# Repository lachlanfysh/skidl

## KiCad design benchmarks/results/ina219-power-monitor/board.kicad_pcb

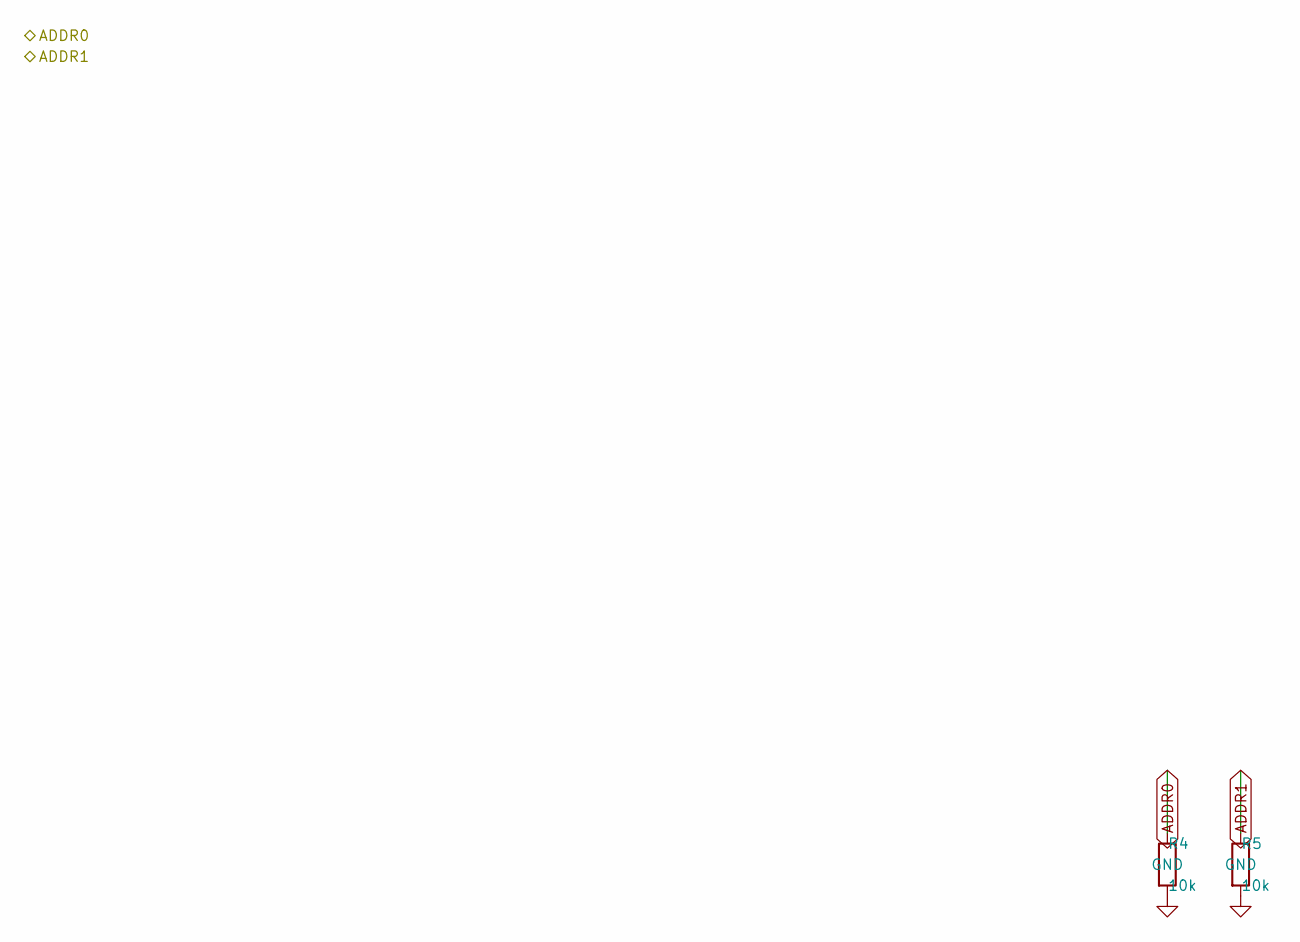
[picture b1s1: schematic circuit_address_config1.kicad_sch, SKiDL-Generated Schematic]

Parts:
R4, R5: 10k; R_0603_1608Metric

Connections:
ADDR0: R4.1; also elsewhere on the board
ADDR1: R5.1; also elsewhere on the board
GND: R4.2, R5.2; also elsewhere on the board

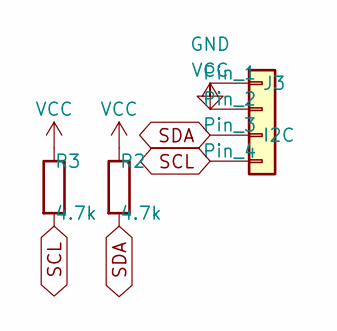
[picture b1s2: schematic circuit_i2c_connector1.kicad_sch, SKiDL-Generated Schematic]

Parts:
J3: I2C; PinHeader_1x04_P2.54mm_Vertical
R2, R3: 4.7k; R_0603_1608Metric

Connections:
GND: J3.1; also elsewhere on the board
SCL: J3.4, R3.2; also elsewhere on the board
SDA: J3.3, R2.2; also elsewhere on the board
VCC: J3.2, R2.1, R3.1; also elsewhere on the board

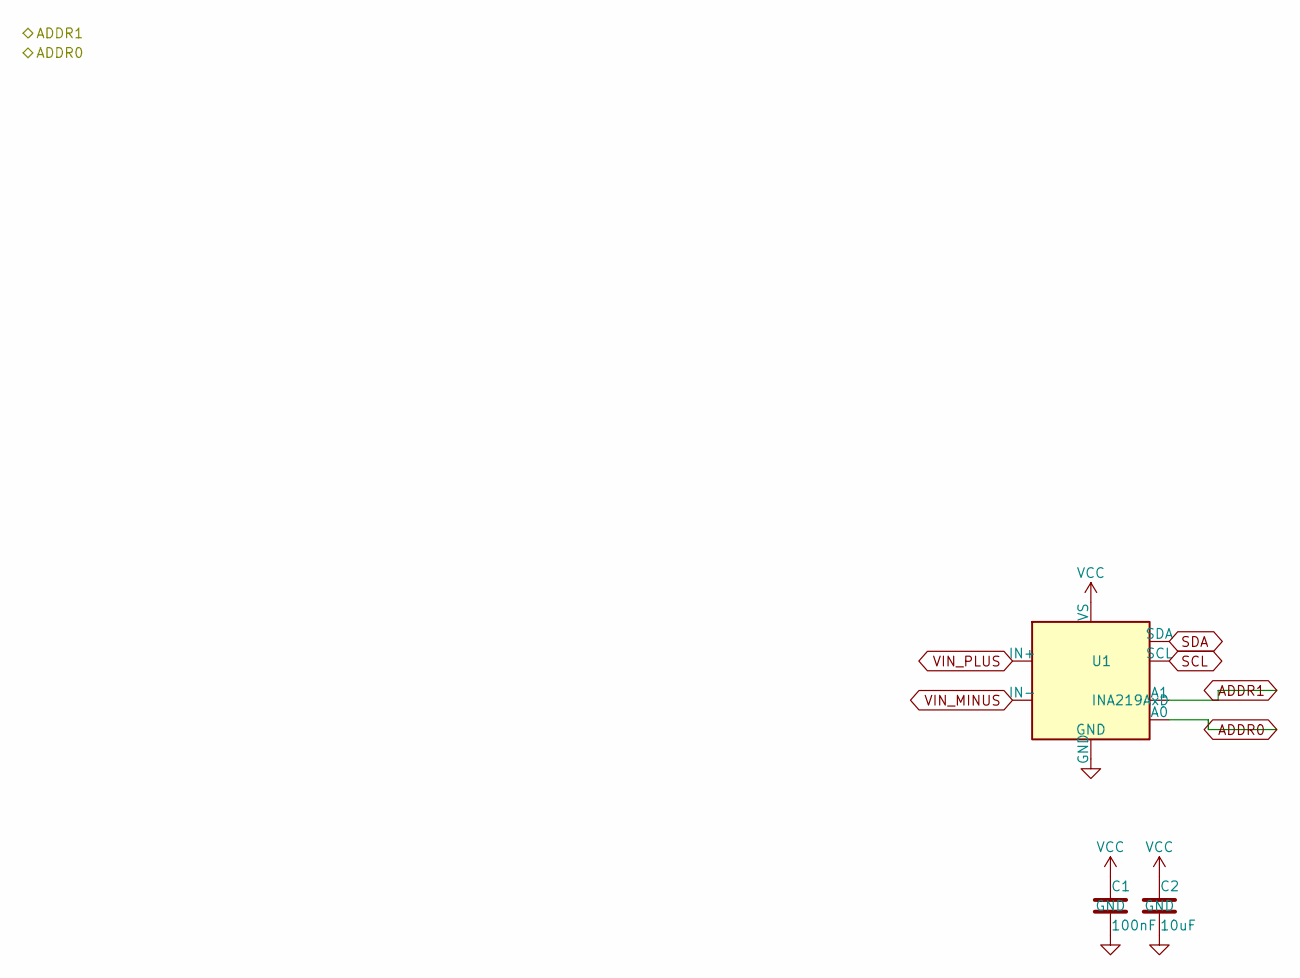
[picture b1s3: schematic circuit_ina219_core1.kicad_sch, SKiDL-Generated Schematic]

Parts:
C1: 100nF; C_0603_1608Metric
C2: 10uF; C_0805_2012Metric
U1: INA219AxD; SOIC-8_3.9x4.9mm_P1.27mm

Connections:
ADDR0: U1.2 (A0); also elsewhere on the board
ADDR1: U1.1 (A1); also elsewhere on the board
GND: C1.2, C2.2, U1.6 (GND); also elsewhere on the board
SCL: U1.4 (SCL); also elsewhere on the board
SDA: U1.3 (SDA); also elsewhere on the board
VCC: C1.1, C2.1, U1.5 (VS); also elsewhere on the board
VIN_MINUS: U1.7 (IN-); also elsewhere on the board
VIN_PLUS: U1.8 (IN+); also elsewhere on the board

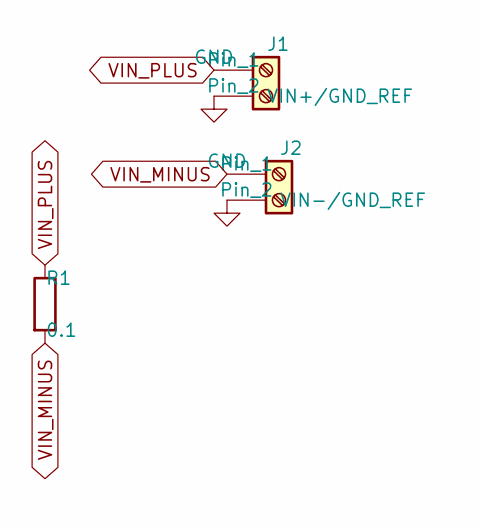
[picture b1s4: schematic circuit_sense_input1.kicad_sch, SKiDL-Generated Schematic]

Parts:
J1: VIN+/GND_REF; TerminalBlock_Phoenix_MKDS-1,5-2-5.08_1x02_P5.08mm_Horizont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
J2: VIN-/GND_REF; TerminalBlock_Phoenix_MKDS-1,5-2-5.08_1x02_P5.08mm_Horizont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
R1: 0.1; R_2512_6332Metric

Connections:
GND: J1.2, J2.2; also elsewhere on the board
VIN_MINUS: J2.1, R1.2; also elsewhere on the board
VIN_PLUS: J1.1, R1.1; also elsewhere on the board

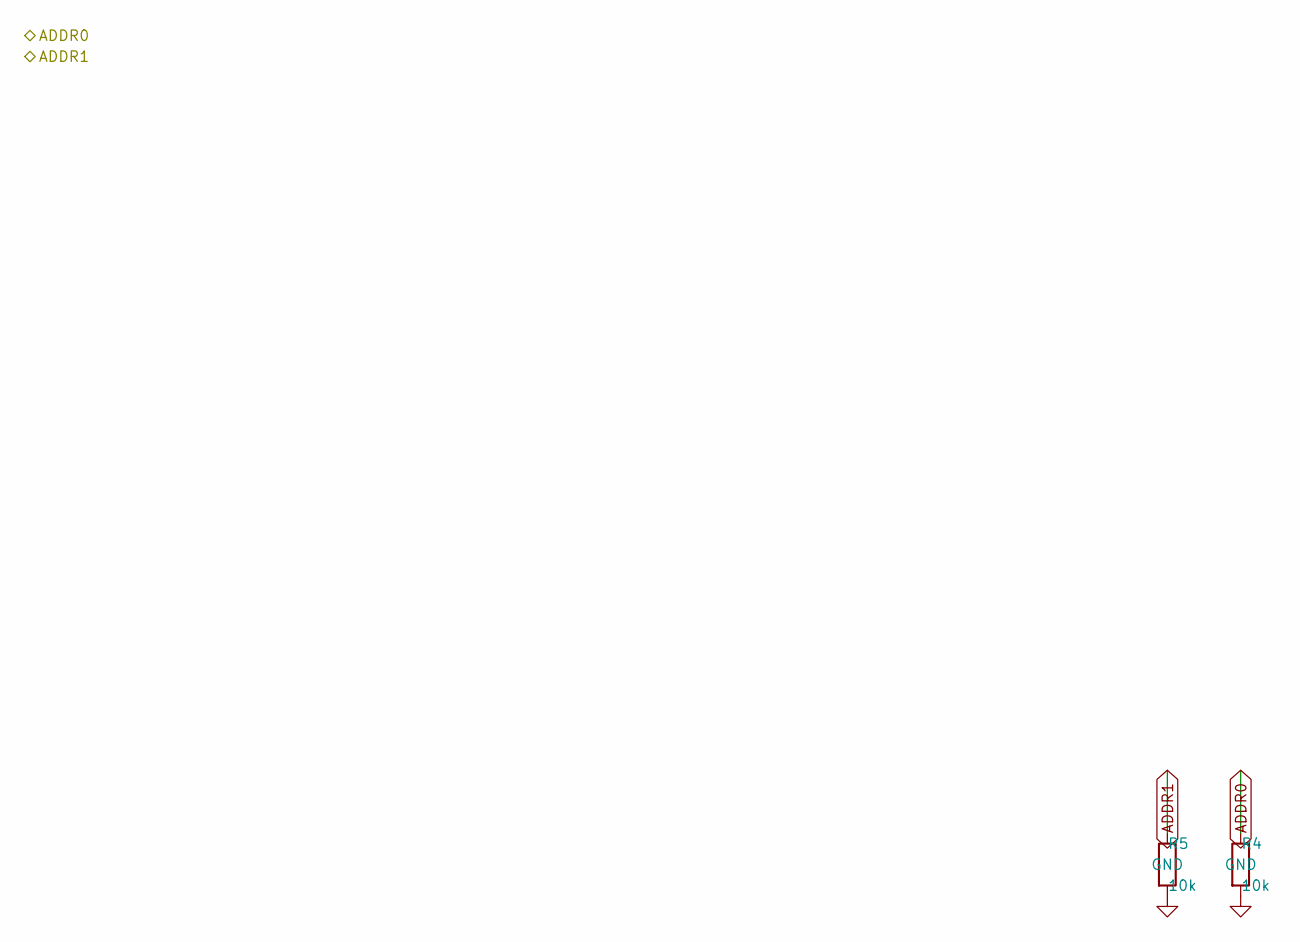
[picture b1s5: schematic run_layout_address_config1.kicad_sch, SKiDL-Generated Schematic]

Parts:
R4, R5: 10k; R_0603_1608Metric

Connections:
ADDR0: R4.1; also elsewhere on the board
ADDR1: R5.1; also elsewhere on the board
GND: R4.2, R5.2; also elsewhere on the board

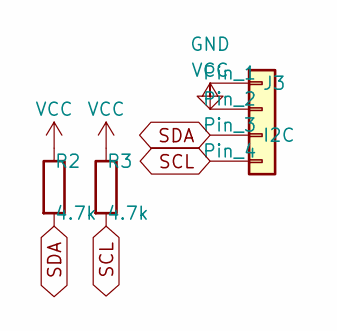
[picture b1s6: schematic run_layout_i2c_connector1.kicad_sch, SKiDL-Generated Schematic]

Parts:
J3: I2C; PinHeader_1x04_P2.54mm_Vertical
R2, R3: 4.7k; R_0603_1608Metric

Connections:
GND: J3.1; also elsewhere on the board
SCL: J3.4, R3.2; also elsewhere on the board
SDA: J3.3, R2.2; also elsewhere on the board
VCC: J3.2, R2.1, R3.1; also elsewhere on the board

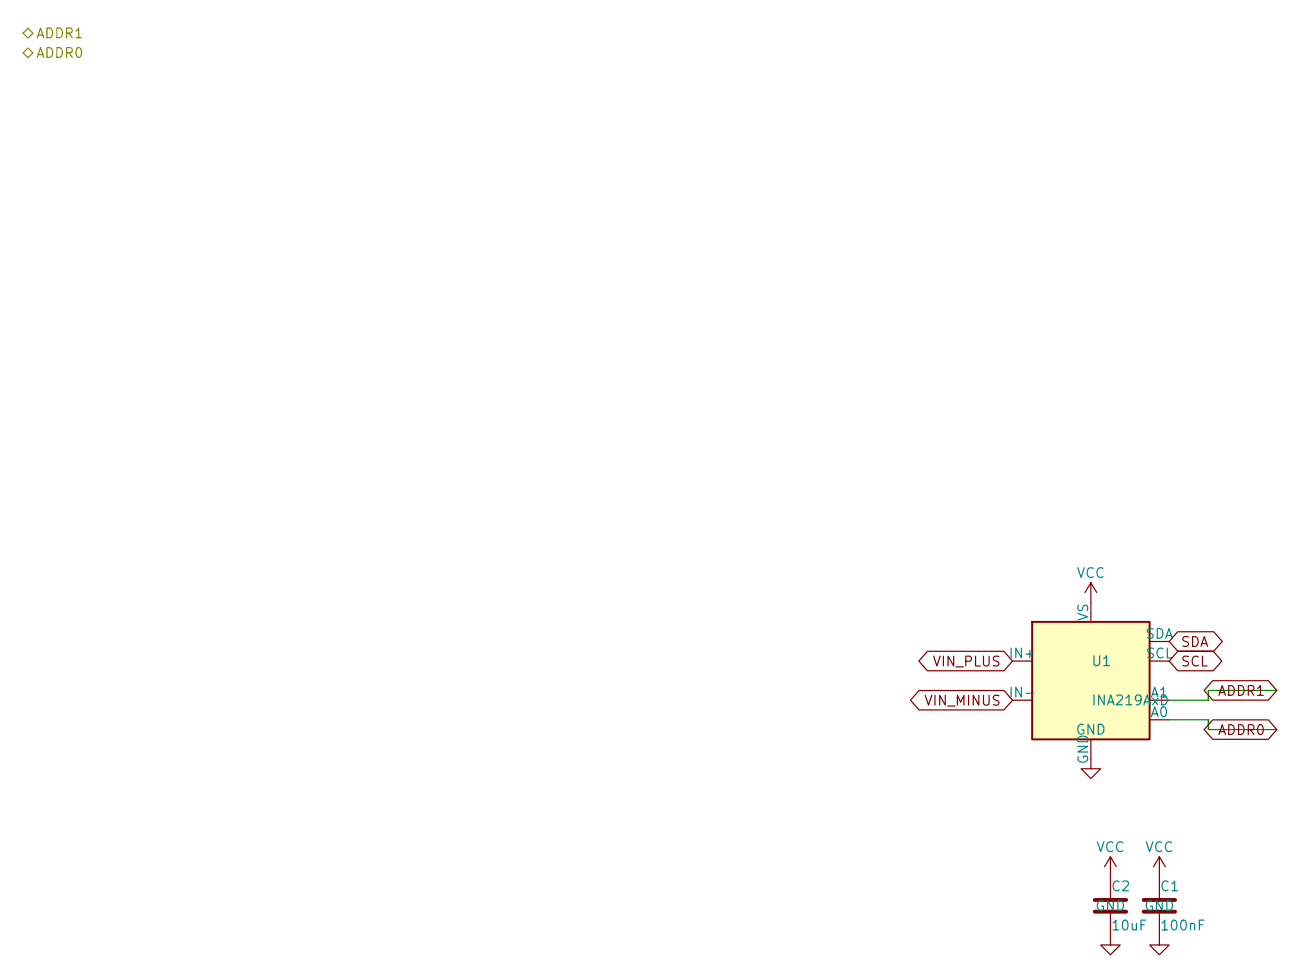
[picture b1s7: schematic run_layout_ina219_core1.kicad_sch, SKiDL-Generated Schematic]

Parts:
C1: 100nF; C_0603_1608Metric
C2: 10uF; C_0805_2012Metric
U1: INA219AxD; SOIC-8_3.9x4.9mm_P1.27mm

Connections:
ADDR0: U1.2 (A0); also elsewhere on the board
ADDR1: U1.1 (A1); also elsewhere on the board
GND: C1.2, C2.2, U1.6 (GND); also elsewhere on the board
SCL: U1.4 (SCL); also elsewhere on the board
SDA: U1.3 (SDA); also elsewhere on the board
VCC: C1.1, C2.1, U1.5 (VS); also elsewhere on the board
VIN_MINUS: U1.7 (IN-); also elsewhere on the board
VIN_PLUS: U1.8 (IN+); also elsewhere on the board

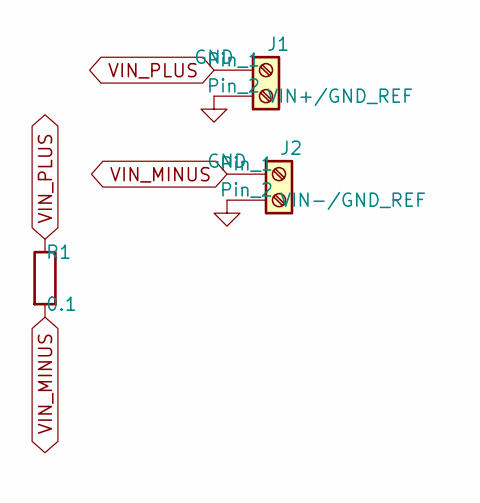
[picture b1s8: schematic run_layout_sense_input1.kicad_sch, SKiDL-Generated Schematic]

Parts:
J1: VIN+/GND_REF; TerminalBlock_Phoenix_MKDS-1,5-2-5.08_1x02_P5.08mm_Horizont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
J2: VIN-/GND_REF; TerminalBlock_Phoenix_MKDS-1,5-2-5.08_1x02_P5.08mm_Horizont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
R1: 0.1; R_2512_6332Metric

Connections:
GND: J1.2, J2.2; also elsewhere on the board
VIN_MINUS: J2.1, R1.2; also elsewhere on the board
VIN_PLUS: J1.1, R1.1; also elsewhere on the board

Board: 2 copper layers, 11 parts (0 on the bottom side), 8 nets, no tracks yet.

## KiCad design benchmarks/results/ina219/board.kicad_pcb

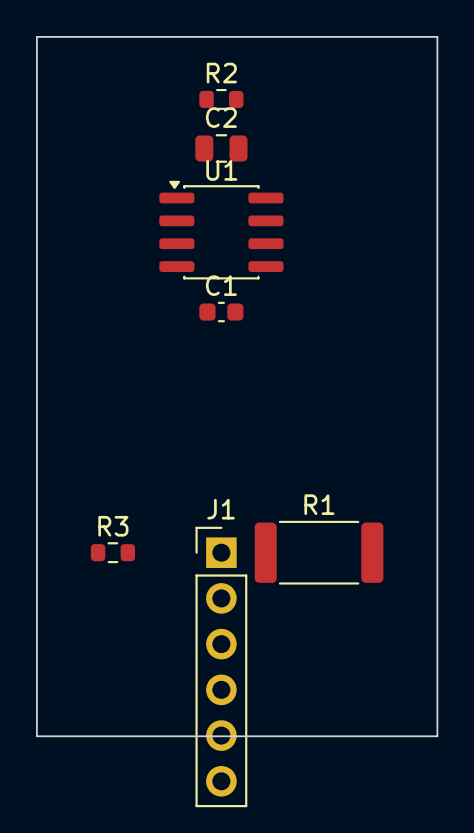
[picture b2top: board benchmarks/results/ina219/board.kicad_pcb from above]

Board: 2 copper layers, 22.2 x 38.9 mm, 7 parts (0 on the bottom side), 6 nets, no tracks yet.

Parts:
C1: 100nF; C_0603_1608Metric
C2: 10uF; C_0805_2012Metric
J1: Breakout_Header; PinHeader_1x06_P2.54mm_Vertical
R1: 0.1; R_2512_6332Metric
R2, R3: 10K; R_0603_1608Metric
U1: INA219BxD; SOIC-8_3.9x4.9mm_P1.27mm

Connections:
GND: C1.2, C2.2, J1.2, U1.1, U1.2, U1.6
SCL: J1.3, R3.2, U1.4
SDA: J1.4, R2.2, U1.3
VCC: C1.1, C2.1, J1.1, R2.1, R3.1, U1.5
VIN+: J1.5, R1.1, U1.8
VIN-: J1.6, R1.2, U1.7

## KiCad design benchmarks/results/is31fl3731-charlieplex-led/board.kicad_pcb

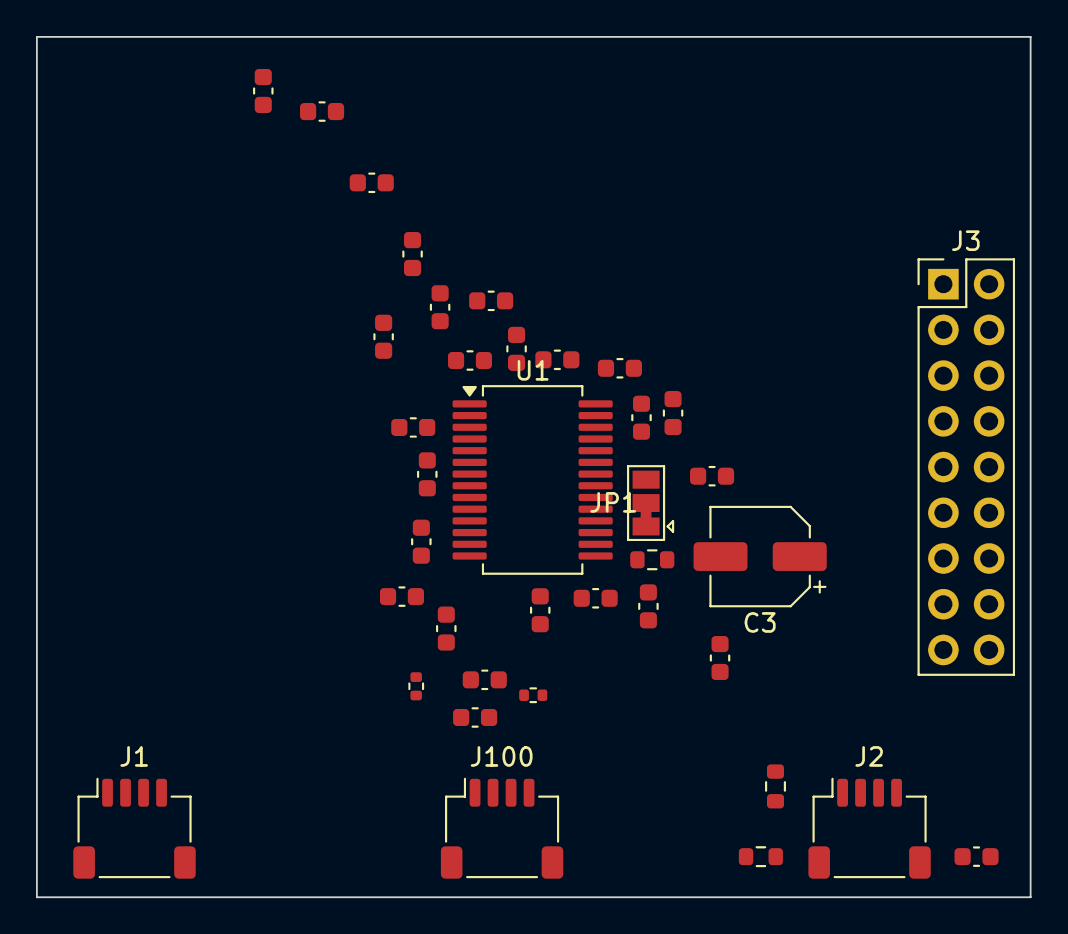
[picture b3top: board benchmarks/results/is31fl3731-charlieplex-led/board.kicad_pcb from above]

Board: 2 copper layers, 55.2 x 47.8 mm, 38 parts (0 on the bottom side), 27 nets, no tracks yet.

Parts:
C1: 220nF; C_0603_1608Metric
C2, C4, C5, C6, C7, C8, C9, C10, C11, C12, C13, C14, C15, C16, C17, C18, C19, C20, C21, C22, C23, C24, C25, C26, C27: 100nF; C_0603_1608Metric
C3: 10uF; CP_Elec_5x5.3
J1, J2: Conn_01x04; JST_SH_SM04B-SRSS-TB_1x04-1MP_P1.00mm_Horizontal
J3: Conn_02x09_Odd_Even; PinHeader_2x09_P2.54mm_Vertical
J100: STEMMA_QT; JST_SH_SM04B-SRSS-TB_1x04-1MP_P1.00mm_Horizontal
JP1: SolderJumper_3_Bridged12; SolderJumper-3_P1.3mm_Bridged12_Pad1.0x1.5mm
R1: 10k; R_0603_1608Metric
R2, R3: 4.7k; R_0603_1608Metric
R100, R101: 4.7K; R_0402_1005Metric
U1: IS31FL3731-SA; SSOP-28_5.3x10.2mm_P0.65mm

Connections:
+3V3: J100.2, R100.1, R101.1
AD: C4.1, JP1.2, U1.18
CA1: C5.1, J3.1, U1.21
CA2: C6.1, J3.3, U1.22
CA3: C7.1, J3.5, U1.23
CA4: C8.1, J3.7, U1.24
CA5: C9.1, J3.9, U1.25
CA6: C10.1, J3.11, U1.26
CA7: C11.1, J3.13, U1.27
CA8: C12.1, J3.15, U1.28
CA9: C13.1, J3.17, U1.1
CB1: C14.1, J3.2, U1.7
CB2: C15.1, J3.4, U1.8
CB3: C16.1, J3.6, U1.9
CB4: C17.1, J3.8, U1.10
CB5: C18.1, J3.10, U1.11
CB6: C19.1, J3.12, U1.12
CB7: C20.1, J3.14, U1.13
CB8: C21.1, J3.16, U1.14
CB9: C22.1, J3.18, U1.15
CFILT: C1.1, C23.1, U1.16
GND: C1.2, C2.2, C3.2, C4.2, C5.2, C6.2, C7.2, C8.2, C9.2, C10.2, C11.2, C12.2, C13.2, C14.2, C15.2, C16.2, C17.2, C18.2, C19.2, C20.2, C21.2, C22.2, C23.2, C24.2, C25.2, C26.2, C27.2, J1.1, J2.1, J100.1, JP1.1, R1.2, U1.5
IN: C24.1, R1.1, U1.17
INTB: C25.1, U1.4
SCL: C26.1, J1.4, J2.4, J100.4, R3.2, R101.2, U1.20
SDA: C27.1, J1.3, J2.3, J100.3, R2.2, R100.2, U1.19
VCC: C2.1, C3.1, J1.2, J2.2, JP1.3, R2.1, R3.1, U1.2, U1.3

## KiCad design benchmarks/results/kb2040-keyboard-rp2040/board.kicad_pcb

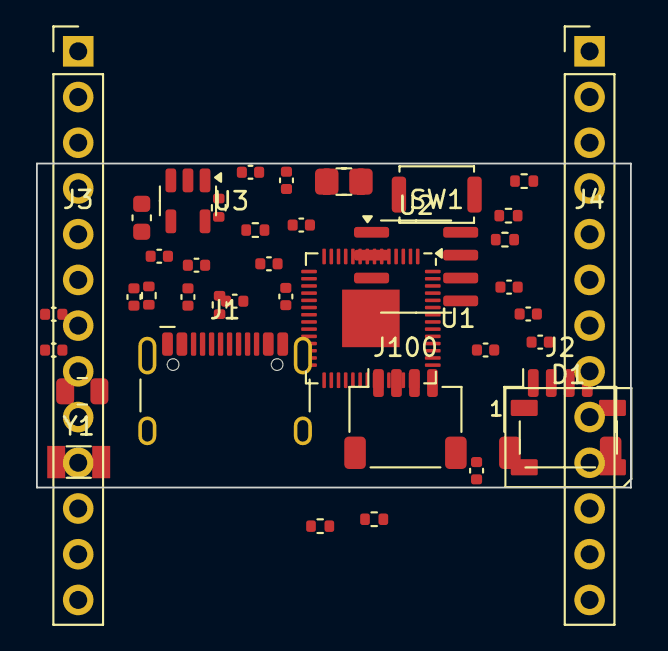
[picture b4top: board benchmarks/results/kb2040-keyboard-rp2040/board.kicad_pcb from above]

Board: 2 copper layers, 33.0 x 18.0 mm, 41 parts (0 on the bottom side), 47 nets, no tracks yet.

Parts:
C1, C2: 15pF; C_0402_1005Metric
C3, C18, C19: 1uF; C_0402_1005Metric
C4, C12, C17: 10uF; C_0805_2012Metric
C5, C6, C7, C8, C9, C10, C11, C13, C14, C15, C16, C20: 100nF; C_0402_1005Metric
C21: 100nF; C_0603_1608Metric
D1: WS2812B; LED_WS2812B_PLCC4_5.0x5.0mm_P3.2mm
J1: USB_C_Receptacle_USB2.0_16P; USB_C_Receptacle_HCTL_HC-TYPE-C-16P-01A
J2: Conn_01x04; JST_SH_SM04B-SRSS-TB_1x04-1MP_P1.00mm_Horizontal
J3, J4: Conn_01x13; PinHeader_1x13_P2.54mm_Vertical
J100: STEMMA_QT; JST_SH_SM04B-SRSS-TB_1x04-1MP_P1.00mm_Horizontal
R1: 200; R_0402_1005Metric
R2, R3: 10K; R_0402_1005Metric
R4, R5: 5.1K; R_0402_1005Metric
R6, R7, R100, R101: 4.7K; R_0402_1005Metric
SW1: SW_Push; SW_Push_SPST_NO_Alps_SKRK
U1: RP2040; QFN-56-1EP_7x7mm_P0.4mm_EP3.2x3.2mm
U2: W25Q128JVS; SOIC-8_3.9x4.9mm_P1.27mm
U3: AP2112K-3.3; SOT-23-5
Y1: 12MHz; Crystal_SMD_3215-2Pin_3.2x1.5mm

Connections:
3V3: C6.1, C7.1, C8.1, C9.1, C10.1, C11.1, C12.1, C13.1, C14.1, C15.1, C19.1, C20.1, D1.1, J2.2, J3.2, R1.1, R2.1, R3.1, R6.1, R7.1, U1.1, U1.10, U1.22, U1.33, U1.42, U1.44, U1.48, U1.49, U2.8, U3.5
+3V3: J100.2, R100.1, R101.1
ADC_AVDD: C5.1, R1.2, U1.43
DVDD: C3.1, C4.1, C21.1, U1.23, U1.45, U1.50
GND: C1.2, C2.2, C3.2, C4.2, C5.2, C6.2, C7.2, C8.2, C9.2, C10.2, C11.2, C12.2, C13.2, C14.2, C15.2, C16.2, C17.2, C18.2, C19.2, C20.2, C21.2, D1.3, J1.A1, J1.A12, J1.B1, J1.B12, J1.S1, J2.1, J3.1, J4.2, J100.1, R4.2, R5.2, SW1.2, U1.19, U1.57, U2.4, U3.2
GPIO0: J3.3, U1.2
GPIO1: J3.4, U1.3
GPIO2: J3.5, U1.4
GPIO3: J3.6, U1.5
GPIO4: J3.7, U1.6
GPIO5: J3.8, U1.7
GPIO6: J3.9, U1.8
GPIO7: J3.10, U1.9
GPIO8: J3.11, U1.11
GPIO9: J3.12, U1.12
GPIO10: J3.13, U1.13
GPIO11: J4.3, U1.14
GPIO12: J4.4, U1.15
GPIO13: J4.5, U1.16
GPIO14: J4.6, U1.17
GPIO15: J4.7, U1.18
GPIO16: D1.4, U1.27
GPIO17: J4.8, U1.28
GPIO18: J2.3, R6.2, U1.29
GPIO19: J2.4, R7.2, U1.30
GPIO20: J4.9, U1.31
GPIO21: J4.10, U1.32
GPIO25: R3.2, SW1.1, U1.37
GPIO26: J4.11, U1.38
GPIO27: J4.12, U1.39
GPIO28: J4.13, U1.40
unnamed: C1.1, U1.20, Y1.1
unnamed: C2.1, U1.21, Y1.2
unnamed: J1.A5, R4.1
unnamed: J1.B5, R5.1
QSPI_SCLK: U1.52, U2.6
QSPI_SD0: U1.53, U2.5
QSPI_SD1: U1.55, U2.2
QSPI_SD2: U1.54, U2.3
QSPI_SD3: U1.51, U2.7
QSPI_SS: U1.56, U2.1
RUN: R2.2, U1.26
SCL: J100.4, R101.2
SDA: J100.3, R100.2
USB_DM: J1.A7, J1.B7, U1.46
USB_DP: J1.A6, J1.B6, U1.47
VBUS: C16.1, C17.1, C18.1, J1.A4, J1.A9, J1.B4, J1.B9, J4.1, U3.1, U3.3

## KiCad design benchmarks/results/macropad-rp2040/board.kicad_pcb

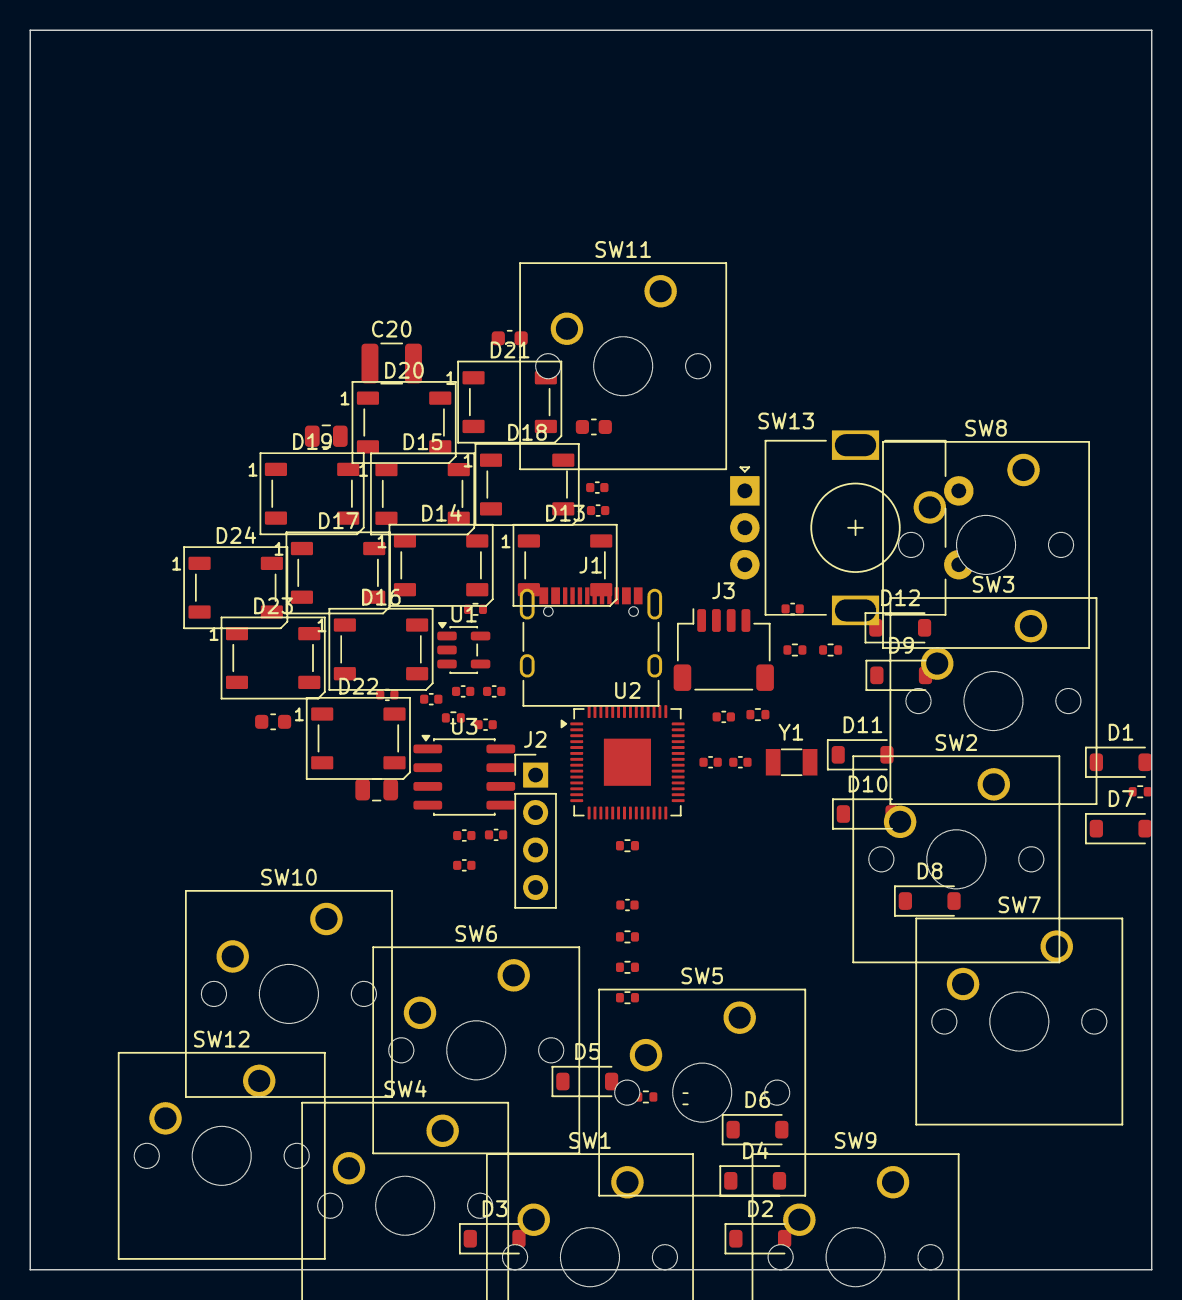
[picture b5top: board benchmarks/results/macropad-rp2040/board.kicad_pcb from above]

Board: 2 copper layers, 76.0 x 84.0 mm, 77 parts (0 on the bottom side), 55 nets, no tracks yet.

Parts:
C1, C4, C6, C7, C8, C9, C10, C11, C12, C13, C16, C21: 100nF; C_0402_1005Metric
C2, C3: 10uF; C_0805_2012Metric
C5: 1uF; C_0402_1005Metric
C14, C15: 15pF; C_0402_1005Metric
C17, C18, C19: 100nF; C_0603_1608Metric
C20: 100uF; C_1210_3225Metric
D1, D2, D3, D4, D5, D6, D7, D8, D9, D10, D11, D12: 1N4148W; D_SOD-123
D13, D14, D15, D16, D17, D18, D19, D20, D21, D22, D23, D24: WS2812B; LED_WS2812B_PLCC4_5.0x5.0mm_P3.2mm
J1: USB_C_Receptacle_USB2.0_14P; USB_C_Receptacle_XKB_U262-16XN-4BVC11
J2: Conn_01x04; PinHeader_1x04_P2.54mm_Vertical
J3: Conn_01x04; JST_SH_SM04B-SRSS-TB_1x04-1MP_P1.00mm_Horizontal
R1, R2: 5.1K; R_0402_1005Metric
R3, R4, R5, R6, R7, R8, R9, R10: 10K; R_0402_1005Metric
R11, R12: 4.7K; R_0402_1005Metric
SW1: KEY0; SW_Cherry_MX_1.00u_PCB
SW2: KEY1; SW_Cherry_MX_1.00u_PCB
SW3: KEY2; SW_Cherry_MX_1.00u_PCB
SW4: KEY3; SW_Cherry_MX_1.00u_PCB
SW5: KEY4; SW_Cherry_MX_1.00u_PCB
SW6: KEY5; SW_Cherry_MX_1.00u_PCB
SW7: KEY6; SW_Cherry_MX_1.00u_PCB
SW8: KEY7; SW_Cherry_MX_1.00u_PCB
SW9: KEY8; SW_Cherry_MX_1.00u_PCB
SW10: KEY9; SW_Cherry_MX_1.00u_PCB
SW11: KEY10; SW_Cherry_MX_1.00u_PCB
SW12: KEY11; SW_Cherry_MX_1.00u_PCB
SW13: RotaryEncoder_Switch; RotaryEncoder_Alps_EC11E-Switch_Vertical_H20mm
U1: AP2112K-3.3; SOT-23-5
U2: RP2040; QFN-56-1EP_7x7mm_P0.4mm_EP3.2x3.2mm
U3: W25Q32JVSS; SOIC-8_3.9x4.9mm_P1.27mm
Y1: 12MHz; Crystal_SMD_3215-2Pin_3.2x1.5mm

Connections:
+3V3: C3.1, C4.1, C6.1, C7.1, C8.1, C9.1, C10.1, C11.1, C12.1, C13.1, C16.1, C21.1, J2.2, J3.2, R3.1, R4.1, R5.1, R6.1, R7.1, R8.1, R9.1, R10.1, R11.1, R12.1, U1.5, U2.1, U2.10, U2.22, U2.33, U2.42, U2.43, U2.44, U2.48, U2.49, U3.8
CC1: J1.A5, R1.1
CC2: J1.B5, R2.1
DVDD: C5.1, U2.23, U2.45, U2.50
ENC_A: R8.2, SW13.A, U2.2
ENC_B: R9.2, SW13.B, U2.3
ENC_SW: R10.2, SW13.S1, U2.5
GND: C1.2, C2.2, C3.2, C4.2, C5.2, C6.2, C7.2, C8.2, C9.2, C10.2, C11.2, C12.2, C13.2, C14.2, C15.2, C16.2, C17.2, C18.2, C19.2, C20.2, C21.2, D13.3, D14.3, D15.3, D16.3, D17.3, D18.3, D19.3, D20.3, D21.3, D22.3, D23.3, D24.3, J1.A1, J1.A12, J1.B1, J1.B12, J1.S1, J2.1, J3.1, R1.2, R2.2, SW13.C, SW13.S2, U1.2, U2.19, U2.57, U3.4
KEY0_D: D1.2, SW1.2
KEY1_D: D2.2, SW2.2
KEY2_D: D3.2, SW3.2
KEY3_D: D4.2, SW4.2
KEY4_D: D5.2, SW5.2
KEY5_D: D6.2, SW6.2
KEY6_D: D7.2, SW7.2
KEY7_D: D8.2, SW8.2
KEY8_D: D9.2, SW9.2
KEY9_D: D10.2, SW10.2
KEY10_D: D11.2, SW11.2
KEY11_D: D12.2, SW12.2
KEY_COL0: D1.1, D5.1, D9.1, R4.2, U2.12
KEY_COL1: D2.1, D6.1, D10.1, R5.2, U2.13
KEY_COL2: D3.1, D7.1, D11.1, R6.2, U2.14
KEY_COL3: D4.1, D8.1, D12.1, R7.2, U2.15
KEY_ROW0: SW1.1, SW2.1, SW3.1, SW4.1, U2.8
KEY_ROW1: SW5.1, SW6.1, SW7.1, SW8.1, U2.9
KEY_ROW2: SW9.1, SW10.1, SW11.1, SW12.1, U2.11
unnamed: R3.2, U2.26
unnamed: J2.3, U2.24
unnamed: J2.4, U2.25
unnamed: C14.1, U2.20, Y1.1
unnamed: C15.1, U2.21, Y1.2
unnamed: U2.56, U3.1
unnamed: U2.52, U3.6
unnamed: U2.53, U3.5
unnamed: U2.55, U3.2
unnamed: U2.54, U3.3
unnamed: U2.51, U3.7
NEOPIXEL_DATA: D13.4, U2.30
NEO_CHAIN_0: D13.2, D14.4
NEO_CHAIN_1: D14.2, D15.4
NEO_CHAIN_2: D15.2, D16.4
NEO_CHAIN_3: D16.2, D17.4
NEO_CHAIN_4: D17.2, D18.4
NEO_CHAIN_5: D18.2, D19.4
NEO_CHAIN_6: D19.2, D20.4
NEO_CHAIN_7: D20.2, D21.4
NEO_CHAIN_8: D21.2, D22.4
NEO_CHAIN_9: D22.2, D23.4
NEO_CHAIN_10: D23.2, D24.4
OLED_SCL: J3.4, R12.2, U2.32
OLED_SDA: J3.3, R11.2, U2.31
USB_DM: J1.A7, J1.B7, U2.46
USB_DP: J1.A6, J1.B6, U2.47
VBUS: C1.1, C2.1, C17.1, C18.1, C19.1, C20.1, D13.1, D14.1, D15.1, D16.1, D17.1, D18.1, D19.1, D20.1, D21.1, D22.1, D23.1, D24.1, J1.A4, J1.A9, J1.B4, J1.B9, U1.1, U1.3

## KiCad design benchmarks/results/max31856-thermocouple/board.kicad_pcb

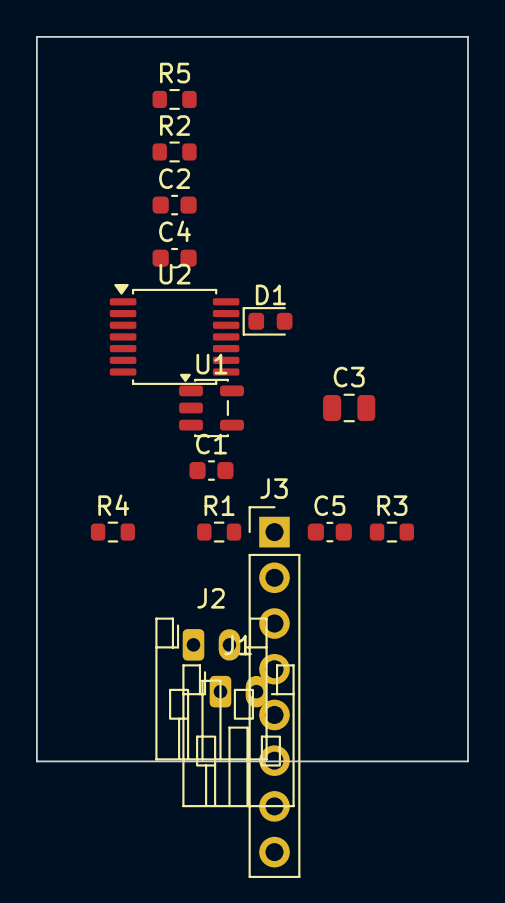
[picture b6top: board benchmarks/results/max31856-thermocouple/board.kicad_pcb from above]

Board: 2 copper layers, 24.0 x 40.2 mm, 16 parts (0 on the bottom side), 13 nets, no tracks yet.

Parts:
C1, C2: 1uF; C_0603_1608Metric
C3: 10uF; C_0805_2012Metric
C4, C5: 100nF; C_0603_1608Metric
D1: GREEN; LED_0603_1608Metric
J1, J2: Conn_01x02; JST_PH_S2B-PH-K_1x02_P2.00mm_Horizontal
J3: Conn_01x08; PinHeader_1x08_P2.54mm_Vertical
R1: 1K; R_0603_1608Metric
R2: 2.2K; R_0603_1608Metric
R3, R4, R5: 10K; R_0603_1608Metric
U1: AP2112K-3.3; SOT-23-5
U2: MAX31856; TSSOP-14_4.4x5mm_P0.65mm

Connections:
+3V3: C2.1, C4.1, C5.1, J3.1, R1.1, R3.1, R4.1, R5.1, U1.5, U2.5, U2.8
DRDY: J3.7, R3.2, U2.7
FAULT: J3.8, R4.2, U2.13
GND: C1.2, C2.2, C3.2, C4.2, C5.2, D1.2, J1.2, J3.2, U1.2, U2.1, U2.14
unnamed: D1.1, R1.2
unnamed: R2.1, U2.2
unnamed: J2.2, R2.2, U2.3
unnamed: J2.1, U2.4
SPI_CS: J3.6, R5.2, U2.9
SPI_SCK: J3.3, U2.10
SPI_SDI: J3.4, U2.12
SPI_SDO: J3.5, U2.11
VIN: C1.1, C3.1, J1.1, U1.1, U1.3

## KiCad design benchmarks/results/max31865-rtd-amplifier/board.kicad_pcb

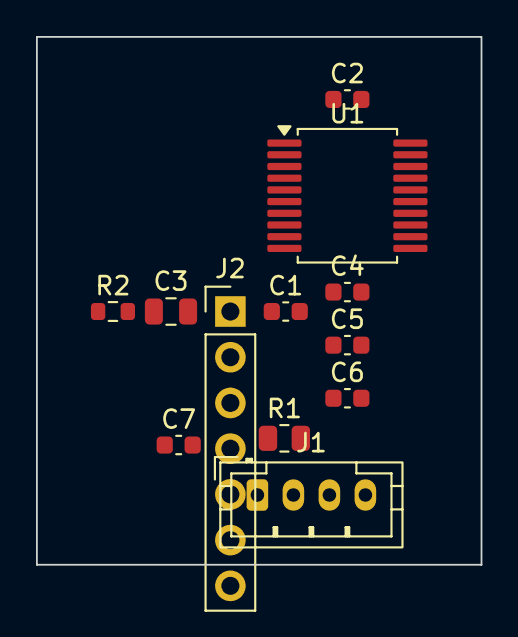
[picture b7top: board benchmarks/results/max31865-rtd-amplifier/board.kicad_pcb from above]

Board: 2 copper layers, 24.7 x 29.3 mm, 12 parts (0 on the bottom side), 11 nets, no tracks yet.

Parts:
C1, C2, C4, C5, C6: 100nF; C_0603_1608Metric
C3: 10uF; C_0805_2012Metric
C7: 1nF; C_0603_1608Metric
J1: RTD_4WIRE; JST_PH_B4B-PH-K_1x04_P2.00mm_Vertical
J2: SPI_HDR; PinHeader_1x07_P2.54mm_Vertical
R1: 4.3K; R_0805_2012Metric
R2: 10K; R_0603_1608Metric
U1: MAX31865; SSOP-20_5.3x7.2mm_P0.65mm

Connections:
BIAS: C4.1, U1.4
GND: C1.2, C2.2, C3.2, C4.2, C5.2, C6.2, J2.2, U1.13, U1.18, U1.19
REFIN+: R1.1, U1.5
REFIN-: R1.2, U1.6
RTDIN+: C5.1, C7.1, J1.2, U1.10
SCLK: J2.3, U1.15
SDI: J2.4, U1.14
SDO: J2.5, U1.17
VDD: C1.1, C2.1, C3.1, J2.1, R2.1, U1.2, U1.3
~CS: J2.6, R2.2, U1.16
~DRDY: J2.7, U1.1

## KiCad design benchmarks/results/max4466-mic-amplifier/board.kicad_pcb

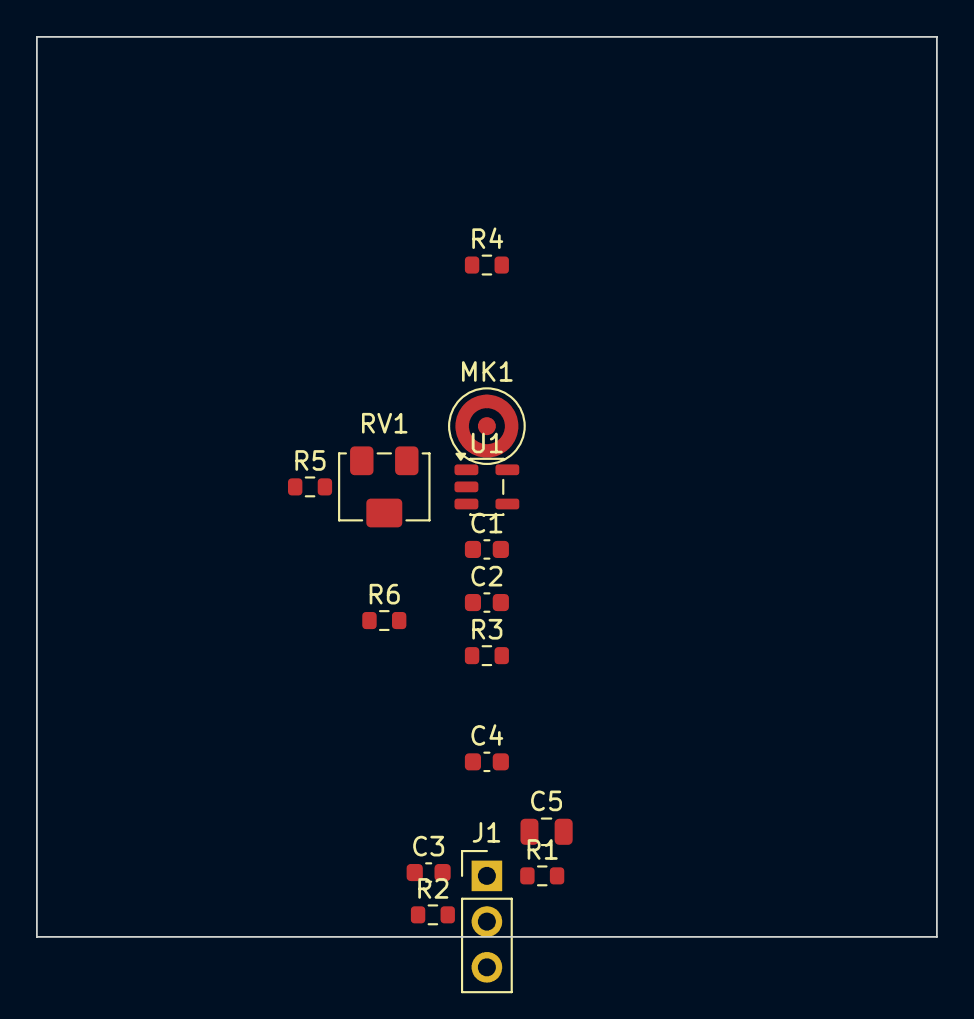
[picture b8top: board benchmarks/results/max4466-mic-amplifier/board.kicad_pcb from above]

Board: 2 copper layers, 50.0 x 50.0 mm, 15 parts (0 on the bottom side), 8 nets, no tracks yet.

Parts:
C1, C2: 100nF; C_0603_1608Metric
C3: 1uF; C_0603_1608Metric
C4: 10pF; C_0603_1608Metric
C5: 10uF; C_0805_2012Metric
J1: Conn_01x03; PinHeader_1x03_P2.54mm_Vertical
MK1: Electret_Mic; CUI_CMC-4013-SMT
R1: 10K; R_0603_1608Metric
R2, R3, R4, R5: 100K; R_0603_1608Metric
R6: 1K; R_0603_1608Metric
RV1: 1K; Potentiometer_Bourns_3214W_Vertical
U1: MAX4466; SOT-23-5

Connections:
AMP_INN: C4.2, R6.1, RV1.2, RV1.3, U1.4
AMP_INP: C2.2, R4.2, U1.3
AUDIO_OUT: C4.1, C5.1, J1.2, R5.1, U1.1
FB_MID: R5.2, RV1.1
GND: C1.2, C3.2, J1.1, MK1.2, R3.2, U1.2
MIC_NODE: C2.1, MK1.1, R1.2
VBIAS: C3.1, R2.2, R3.1, R4.1, R6.2
VCC: C1.1, J1.3, R1.1, R2.1, U1.5
